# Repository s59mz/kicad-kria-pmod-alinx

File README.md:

# kicad-kria-pmod-alinx
Kria KR260 4x PMOD to Alinx modules Adapter

Schematic:
[kicad-kria-pmod-alinx.pdf](kicad-kria-pmod-alinx.pdf)

BOM:
[kicad-kria-pmod-alinx.csv](kicad-kria-pmod-alinx.csv)

Gerbers:
[gerbers.zip](https://github.com/s59mz/kicad-kria-pmod-alinx/raw/main/gerbers.zip)

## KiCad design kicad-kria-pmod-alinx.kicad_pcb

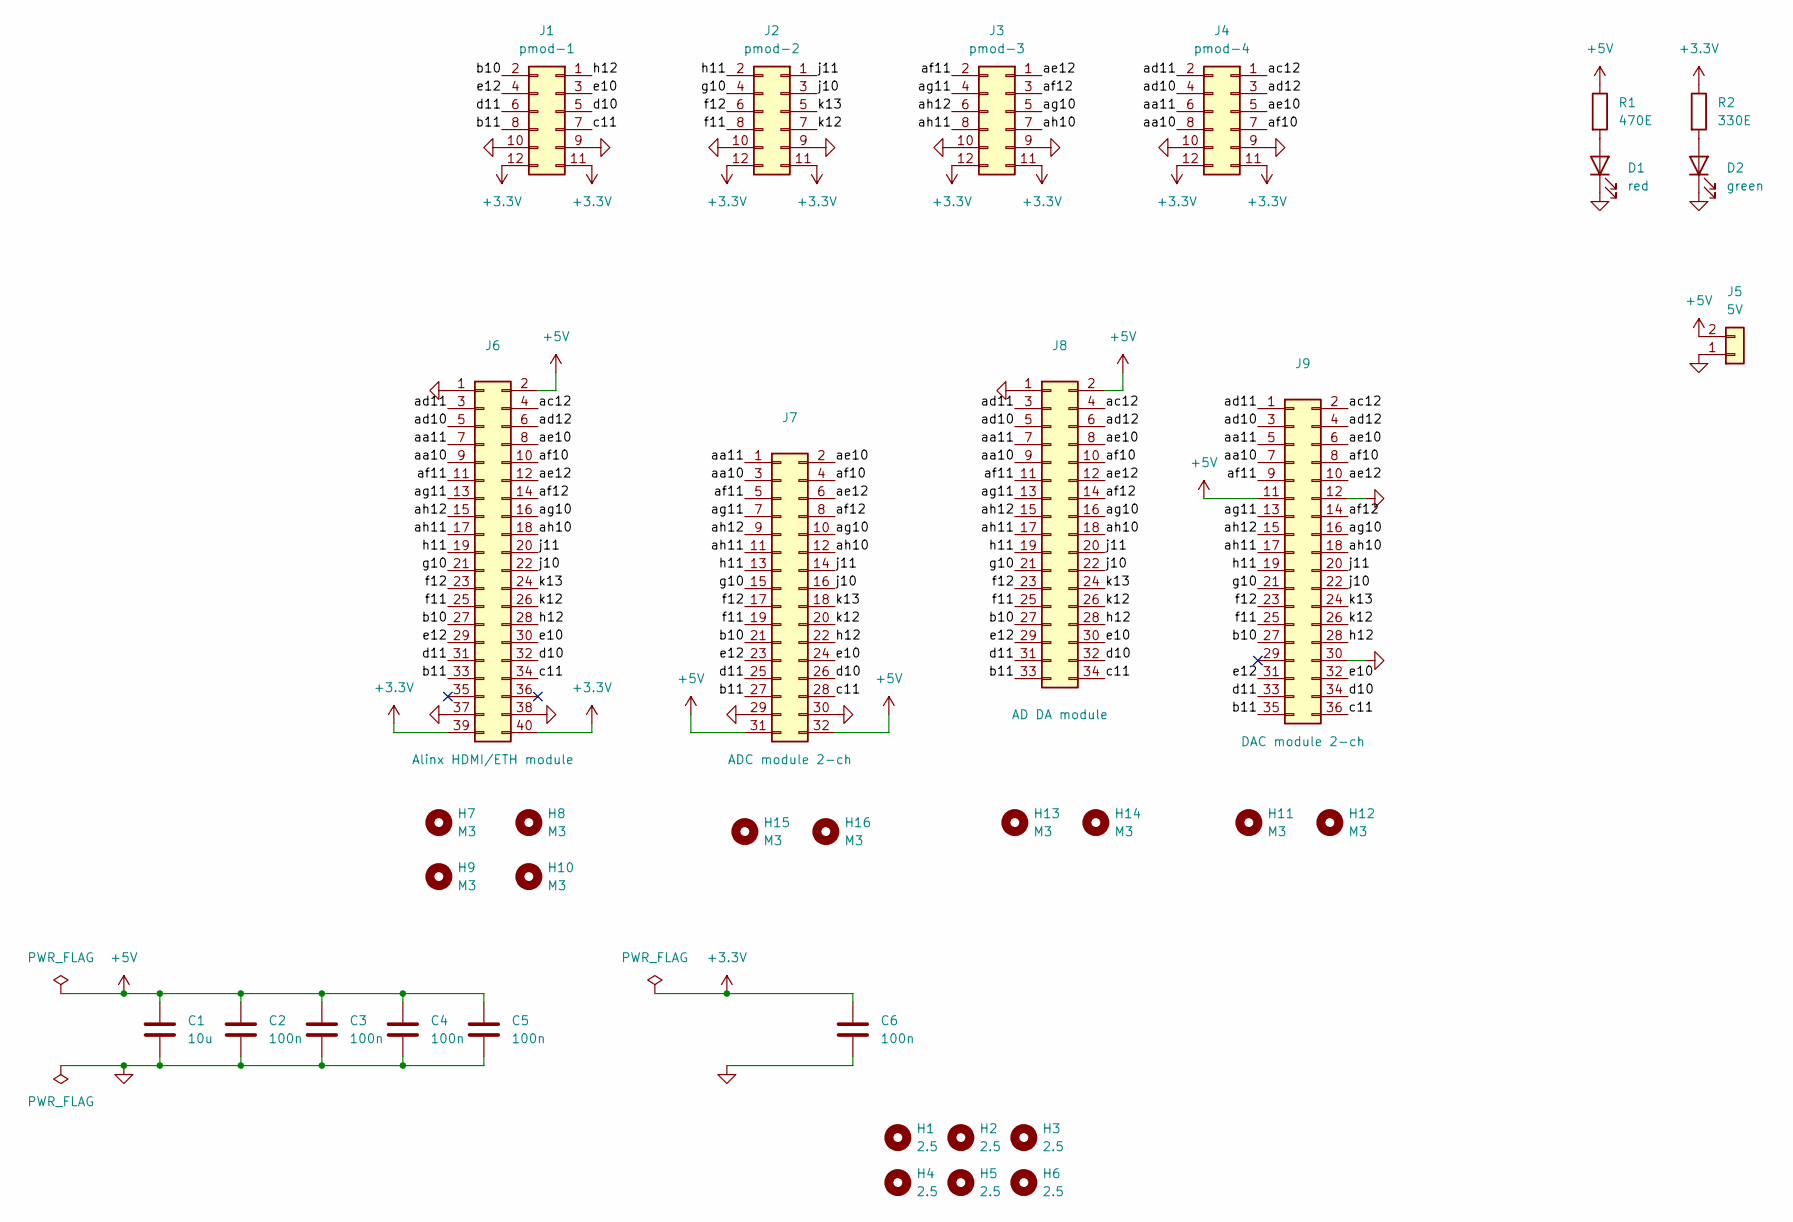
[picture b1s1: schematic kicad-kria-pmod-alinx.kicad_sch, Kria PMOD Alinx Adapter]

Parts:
C1: 10u; C_0603_1608Metric_Pad1.08x0.95mm_HandSolder
C2, C3, C4, C5, C6: 100n; C_0603_1608Metric_Pad1.08x0.95mm_HandSolder
D1: red; LED_0603_1608Metric_Pad1.05x0.95mm_HandSolder
D2: green; LED_0603_1608Metric_Pad1.05x0.95mm_HandSolder
H1, H2, H3, H4, H5, H6: 2.5; MountingHole_2.5mm
H7, H8, H9, H10, H11, H12, H13, H14, H15, H16: M3; MountingHole_3.2mm_M3
J1: pmod-1; PinHeader_2x06_P2.54mm_Horizontal
J2: pmod-2; PinHeader_2x06_P2.54mm_Horizontal
J3: pmod-3; PinHeader_2x06_P2.54mm_Horizontal
J4: pmod-4; PinHeader_2x06_P2.54mm_Horizontal
J5: 5V; PinHeader_1x02_P2.54mm_Vertical
J6: Alinx HDMI/ETH module; PinHeader_2x20_P2.54mm_Vertical
J7: ADC module 2-ch; PinHeader_2x16_P2.54mm_Vertical
J8: AD DA module; PinHeader_2x17_P2.54mm_Vertical
J9: DAC module 2-ch; PinHeader_2x18_P2.54mm_Vertical
R1: 470E; R_0603_1608Metric_Pad0.98x0.95mm_HandSolder
R2: 330E; R_0603_1608Metric_Pad0.98x0.95mm_HandSolder

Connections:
+3.3V: C6.1, J1.11, J1.12, J2.11, J2.12, J3.11, J3.12, J4.11, J4.12, J6.39, J6.40, R2.1
+5V: C1.1, C2.1, C3.1, C4.1, C5.1, J5.2, J6.2, J7.31, J7.32, J8.2, J9.11, R1.1
/aa10: J4.8, J6.9, J7.3, J8.9, J9.7
/aa11: J4.6, J6.7, J7.1, J8.7, J9.5
/ac12: J4.1, J6.4, J8.4, J9.2
/ad10: J4.4, J6.5, J8.5, J9.3
/ad11: J4.2, J6.3, J8.3, J9.1
/ad12: J4.3, J6.6, J8.6, J9.4
/ae10: J4.5, J6.8, J7.2, J8.8, J9.6
/ae12: J3.1, J6.12, J7.6, J8.12, J9.10
/af10: J4.7, J6.10, J7.4, J8.10, J9.8
/af11: J3.2, J6.11, J7.5, J8.11, J9.9
/af12: J3.3, J6.14, J7.8, J8.14, J9.14
/ag10: J3.5, J6.16, J7.10, J8.16, J9.16
/ag11: J3.4, J6.13, J7.7, J8.13, J9.13
/ah10: J3.7, J6.18, J7.12, J8.18, J9.18
/ah11: J3.8, J6.17, J7.11, J8.17, J9.17
/ah12: J3.6, J6.15, J7.9, J8.15, J9.15
/b10: J1.2, J6.27, J7.21, J8.27, J9.27
/b11: J1.8, J6.33, J7.27, J8.33, J9.35
/c11: J1.7, J6.34, J7.28, J8.34, J9.36
/d10: J1.5, J6.32, J7.26, J8.32, J9.34
/d11: J1.6, J6.31, J7.25, J8.31, J9.33
/e10: J1.3, J6.30, J7.24, J8.30, J9.32
/e12: J1.4, J6.29, J7.23, J8.29, J9.31
/f11: J2.8, J6.25, J7.19, J8.25, J9.25
/f12: J2.6, J6.23, J7.17, J8.23, J9.23
/g10: J2.4, J6.21, J7.15, J8.21, J9.21
/h11: J2.2, J6.19, J7.13, J8.19, J9.19
/h12: J1.1, J6.28, J7.22, J8.28, J9.28
/j10: J2.3, J6.22, J7.16, J8.22, J9.22
/j11: J2.1, J6.20, J7.14, J8.20, J9.20
/k12: J2.7, J6.26, J7.20, J8.26, J9.26
/k13: J2.5, J6.24, J7.18, J8.24, J9.24
GND: C1.2, C2.2, C3.2, C4.2, C5.2, C6.2, D1.1 (K), D2.1 (K), J1.9, J1.10, J2.9, J2.10, J3.9, J3.10, J4.9, J4.10, J5.1, J6.1, J6.37, J6.38, J7.29, J7.30, J8.1, J9.12, J9.30
unnamed: D1.2 (A), R1.2
unnamed: D2.2 (A), R2.2

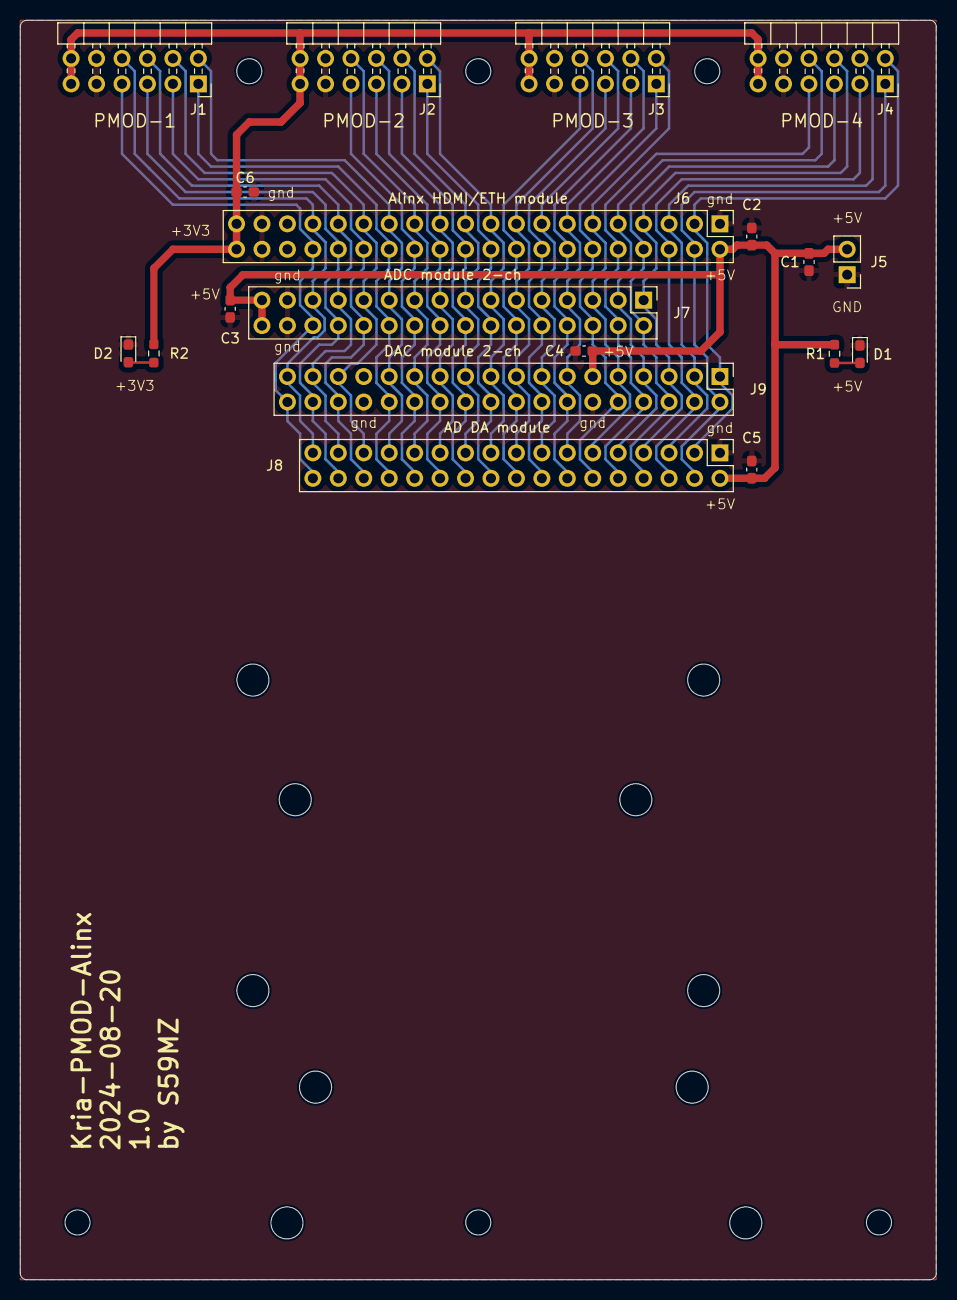
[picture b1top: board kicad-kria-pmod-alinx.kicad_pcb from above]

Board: 2 copper layers, 91.4 x 125.7 mm, 35 parts (0 on the bottom side), 37 nets.

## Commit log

2024-08-18 schematic and module holes
